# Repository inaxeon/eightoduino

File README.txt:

This is the source code for an Intel 8086 based micro board

Full details are here:
http://tech.mattmillman.com/projects/8od/

Directory contents:

app_*:

Example "boot from flash" applications for 8OD.

bootrom:

The source code for 8OD's standard bootrom which is used
for serial download, to and booting from SPI flash.

eprom_with_app:

Contains an example of how to make an image which runs from
EPROM instead of using the standard bootrom. RAM is still
required to store the stack and data.

Interrupts are not currently supported.

sys:

Sources used by all other subdirectories

*** CAVEAT EMPTOR ***

All code here must be compiled with Open WATCOM version 1.7a

I have tried newer versions - my findings:

Version 1.8
Version 1.9

* Copy attribute (linker script) seems to be broken.
  Linker does not copy data from source segment to destination
  segments, breaking the bootrom builds.

* There seems to be some kind of new enforcement mechanism
  which checks that no code or data lies outside of the active 64KB
  segment. 8OD apps technically do have a little of this to assist
  the bootstrapping process, but it is not an actual problem.
  'wlink' in these versions believes otherwise, and fails to link.

Version 2.0 BETA

* Still has the copy attribute bug

* The segment extent enforcement seems to have disappeared in this
  version, promising...
  
* When I tried to build an app, the .hex were mostly garbage data with
  the majority of the exectuable code missing, suffice to say that this
  version is completely unuseable (at the time I tried it).

Version 1.7a observed problems

* This version isn't perfect either. See in 'app_gravitech_shield' where
  I have had to add dummy code to stop the linker from crashing. I spent
  quite a lot of time investigating this and never got to the bottom
  of it.

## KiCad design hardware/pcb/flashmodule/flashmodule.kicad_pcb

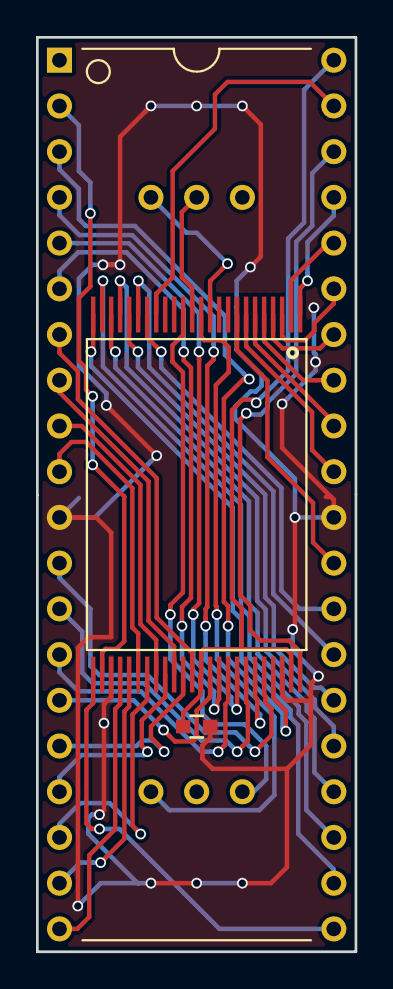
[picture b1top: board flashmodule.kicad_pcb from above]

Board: 2 copper layers, 17.7 x 50.8 mm, 5 parts (0 on the bottom side), 42 nets.

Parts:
C1: 0.1; C_0603
P1, P2: CONN_01X03; Socket_Strip_Straight_1x03
U1: 28F400; TSOP48
U2: M27C4002; DIP-40__600

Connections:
/A0: U1.25, U2.21
/A1: U1.24, U2.22
/A2: U1.23, U2.23
/A3: U1.22, U2.24
/A4: U1.21, U2.25
/A5: U1.20, U2.26
/A6: U1.19, U2.27
/A7: U1.18, U2.28
/A8: U1.8, U2.29
/A9: U1.7, U2.31
/A10: U1.6, U2.32
/A11: U1.5, U2.33
/A12: U1.4, U2.34
/A13: U1.3, U2.35
/A14: U1.2, U2.36
/A15: U1.1, U2.37
/A16: U1.48, U2.38
/A17: U1.17, U2.39
/D0: U1.29, U2.19
/D1: U1.31, U2.18
/D2: U1.33, U2.17
/D3: U1.35, U2.16
/D4: U1.38, U2.15
/D5: U1.40, U2.14
/D6: U1.42, U2.13
/D7: U1.44, U2.12
/D8: U1.30, U2.10
/D9: U1.32, U2.9
/D10: U1.34, U2.8
/D11: U1.36, U2.7
/D12: U1.39, U2.6
/D13: U1.41, U2.5
/D14: U1.43, U2.4
/D15: U1.45, U2.3
/VPP: P1.2, U1.13
/~CS: U1.26, U2.2
/~RD: U1.28, U2.20
/~RESET: P2.1, U1.12
/~WP: P2.3, U1.14
/~WR: P1.1, U1.11
GND: C1.2, U1.27, U1.46, U2.11, U2.30
VCC: C1.1, U1.37, U1.47, U2.40

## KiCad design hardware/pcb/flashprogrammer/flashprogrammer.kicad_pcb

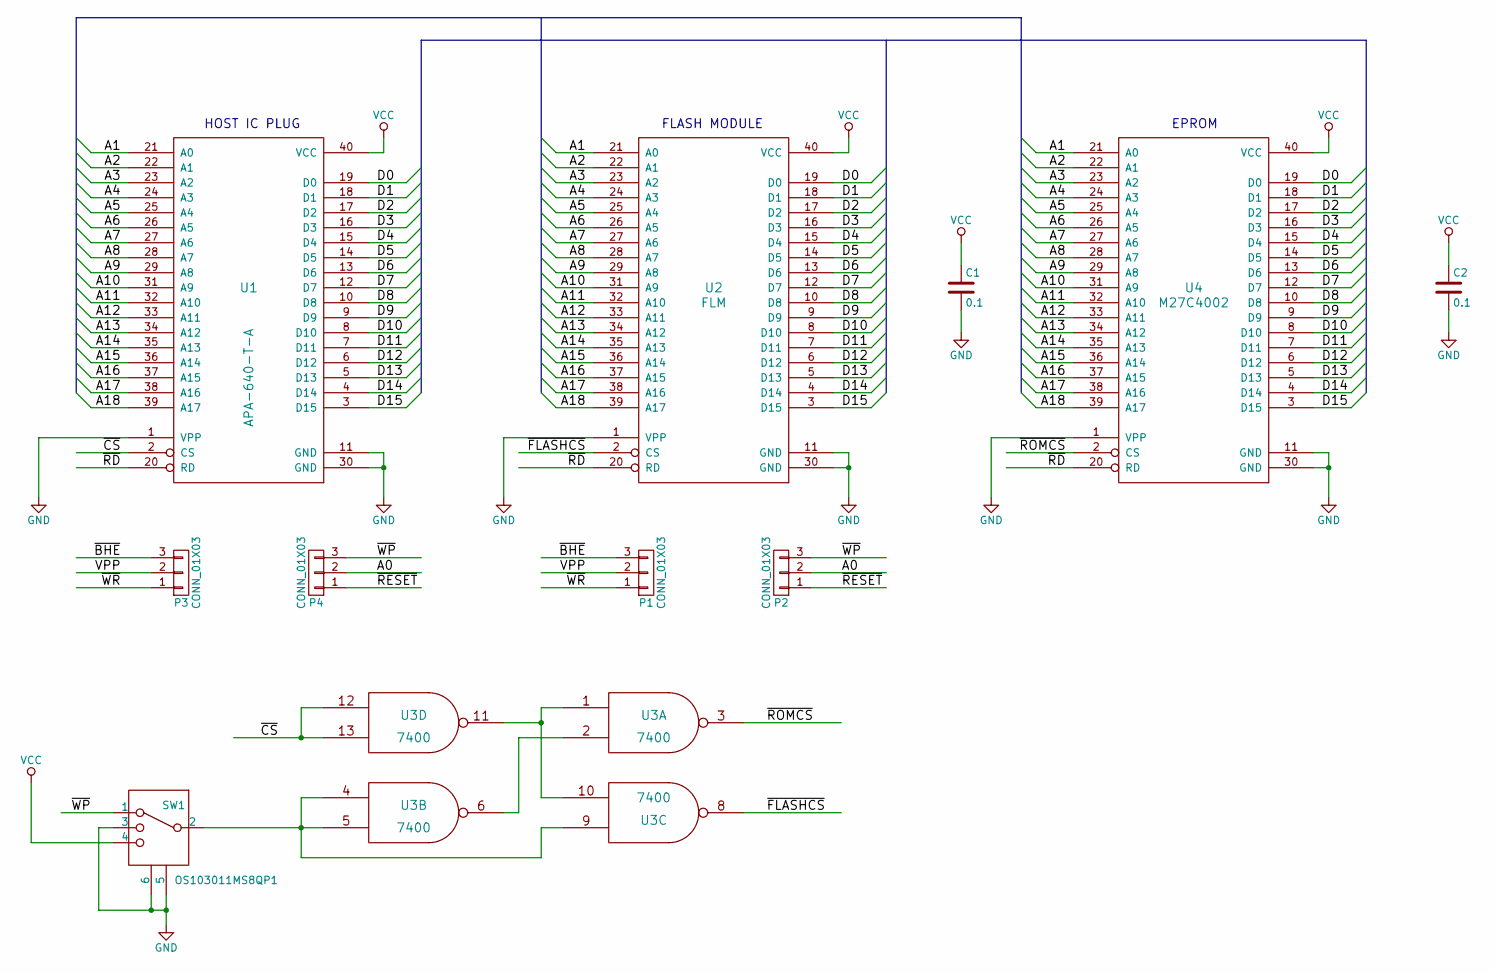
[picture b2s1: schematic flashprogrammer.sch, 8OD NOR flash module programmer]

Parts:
C1, C2: 0.1; C_0603
P1, P2, P3, P4: CONN_01X03; Socket_Strip_Straight_1x03
SW1: OS103011MS8QP1; SW_SP3T
U1: APA-640-T-A; DIP-40__600
U2: FLM; DIP-40__600
U3: 7400; SOIC-14_3.9x8.7mm_Pitch1.27mm
U4: M27C4002; DIP-40__600

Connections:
/A0: P2.2, P4.2
/A1: U1.21 (A0), U2.21 (A0), U4.21 (A0)
/A2: U1.22 (A1), U2.22 (A1), U4.22 (A1)
/A3: U1.23 (A2), U2.23 (A2), U4.23 (A2)
/A4: U1.24 (A3), U2.24 (A3), U4.24 (A3)
/A5: U1.25 (A4), U2.25 (A4), U4.25 (A4)
/A6: U1.26 (A5), U2.26 (A5), U4.26 (A5)
/A7: U1.27 (A6), U2.27 (A6), U4.27 (A6)
/A8: U1.28 (A7), U2.28 (A7), U4.28 (A7)
/A9: U1.29 (A8), U2.29 (A8), U4.29 (A8)
/A10: U1.31 (A9), U2.31 (A9), U4.31 (A9)
/A11: U1.32 (A10), U2.32 (A10), U4.32 (A10)
/A12: U1.33 (A11), U2.33 (A11), U4.33 (A11)
/A13: U1.34 (A12), U2.34 (A12), U4.34 (A12)
/A14: U1.35 (A13), U2.35 (A13), U4.35 (A13)
/A15: U1.36 (A14), U2.36 (A14), U4.36 (A14)
/A16: U1.37 (A15), U2.37 (A15), U4.37 (A15)
/A17: U1.38 (A16), U2.38 (A16), U4.38 (A16)
/A18: U1.39 (A17), U2.39 (A17), U4.39 (A17)
/D0: U1.19 (D0), U2.19 (D0), U4.19 (D0)
/D1: U1.18 (D1), U2.18 (D1), U4.18 (D1)
/D2: U1.17 (D2), U2.17 (D2), U4.17 (D2)
/D3: U1.16 (D3), U2.16 (D3), U4.16 (D3)
/D4: U1.15 (D4), U2.15 (D4), U4.15 (D4)
/D5: U1.14 (D5), U2.14 (D5), U4.14 (D5)
/D6: U1.13 (D6), U2.13 (D6), U4.13 (D6)
/D7: U1.12 (D7), U2.12 (D7), U4.12 (D7)
/D8: U1.10 (D8), U2.10 (D8), U4.10 (D8)
/D9: U1.9 (D9), U2.9 (D9), U4.9 (D9)
/D10: U1.8 (D10), U2.8 (D10), U4.8 (D10)
/D11: U1.7 (D11), U2.7 (D11), U4.7 (D11)
/D12: U1.6 (D12), U2.6 (D12), U4.6 (D12)
/D13: U1.5 (D13), U2.5 (D13), U4.5 (D13)
/D14: U1.4 (D14), U2.4 (D14), U4.4 (D14)
/D15: U1.3 (D15), U2.3 (D15), U4.3 (D15)
/VPP: P1.2, P3.2
/~BHE: P1.3, P3.3
/~CS: U1.2 (CS), U3.12, U3.13
/~FLASHCS: U2.2 (CS), U3.8
/~RD: U1.20 (RD), U2.20 (RD), U4.20 (RD)
/~RESET: P2.1, P4.1
/~ROMCS: U3.3, U4.2 (CS)
/~WP: P2.3, P4.3, SW1.1
/~WR: P1.1, P3.1
GND: C1.2, C2.2, SW1.3, SW1.5, SW1.6, U1.1 (VPP), U1.11 (GND), U1.30 (GND), U2.1 (VPP), U2.11 (GND), U2.30 (GND), U3.7 (GND), U4.1 (VPP), U4.11 (GND), U4.30 (GND)
unnamed: SW1.2, U3.4, U3.5, U3.9
unnamed: U3.1, U3.10, U3.11
unnamed: U3.2, U3.6
VCC: C1.1, C2.1, SW1.4, U1.40 (VCC), U2.40 (VCC), U3.14 (VCC), U4.40 (VCC)

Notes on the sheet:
HOST IC PLUG
FLASH MODULE
EPROM

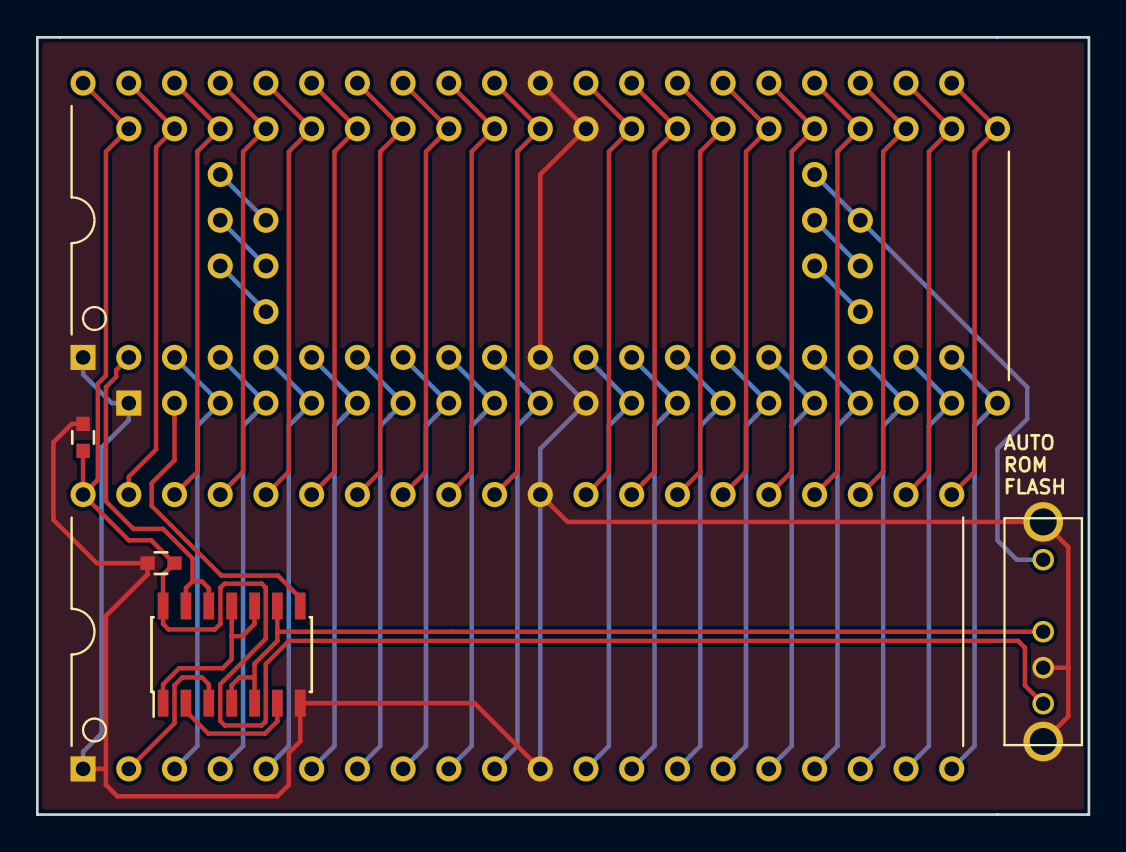
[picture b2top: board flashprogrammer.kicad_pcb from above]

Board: 2 copper layers, 58.4 x 43.2 mm, 11 parts (0 on the bottom side), 49 nets.

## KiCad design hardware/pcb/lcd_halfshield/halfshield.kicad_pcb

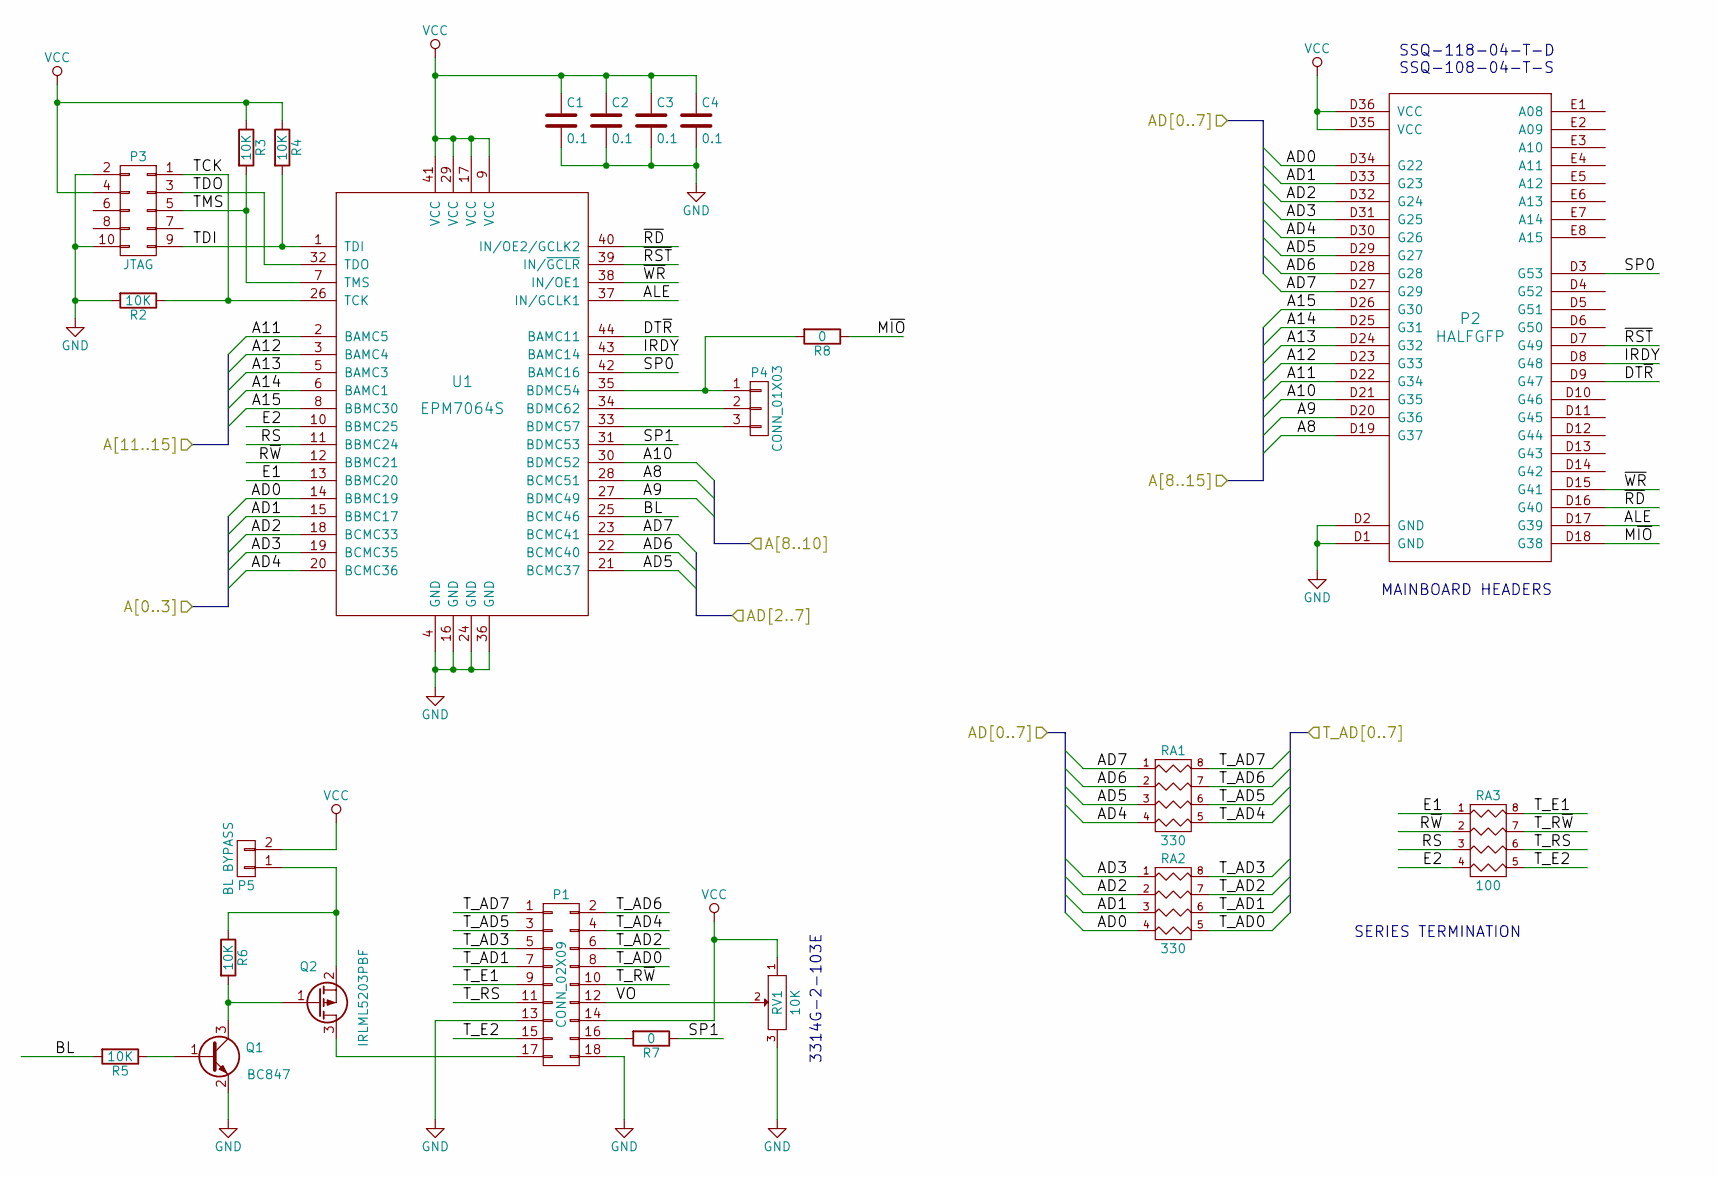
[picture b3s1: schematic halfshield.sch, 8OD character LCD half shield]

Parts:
C1, C2, C3, C4: 0.1; C_0603
P1: CONN_02X09; PIN_ARRAY_9x2
P2: HALFGFP; DUINO
P3: JTAG; PIN_ARRAY_5x2
P4: CONN_01X03; Pin_Header_Straight_1x03
P5: BL BYPASS; Pin_Header_Straight_1x02
Q1: BC847; SOT-23
Q2: IRLML5203PBF
R2, R3, R4, R5, R6: 10K; R_0603
R7, R8: 0; R_0603
RA1, RA2: 330; R_Array_Convex_4x0603
RA3: 100; R_Array_Convex_4x0603
RV1: 10K; POT_SMD
U1: EPM7064S; TQFP-44_10x10mm_Pitch0.8mm

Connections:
/A8: P2.D19 (G37), U1.28 (BCMC51)
/A9: P2.D20 (G36), U1.27 (BDMC49)
/A10: P2.D21 (G35), U1.30 (BDMC52)
/A11: P2.D22 (G34), U1.2 (BAMC5)
/A12: P2.D23 (G33), U1.3 (BAMC4)
/A13: P2.D24 (G32), U1.5 (BAMC3)
/A14: P2.D25 (G31), U1.6 (BAMC1)
/A15: P2.D26 (G30), U1.8 (BBMC30)
/AD0: P2.D34 (G22), RA2.4, U1.14 (BBMC19)
/AD1: P2.D33 (G23), RA2.3, U1.15 (BBMC17)
/AD2: P2.D32 (G24), RA2.2, U1.18 (BCMC33)
/AD3: P2.D31 (G25), RA2.1, U1.19 (BCMC35)
/AD4: P2.D30 (G26), RA1.4, U1.20 (BCMC36)
/AD5: P2.D29 (G27), RA1.3, U1.21 (BCMC37)
/AD6: P2.D28 (G28), RA1.2, U1.22 (BCMC40)
/AD7: P2.D27 (G29), RA1.1, U1.23 (BCMC41)
/ALE: P2.D17 (G39), U1.37 (IN/GCLK1)
/BL: R5.2, U1.25 (BCMC46)
/DT~R: P2.D9 (G47), U1.44 (BAMC11)
/E1: RA3.1, U1.13 (BBMC20)
/E2: RA3.4, U1.10 (BBMC25)
/IRDY: P2.D8 (G48), U1.43 (BAMC14)
/M~IO: P2.D18 (G38), R8.1
/RS: RA3.3, U1.11 (BBMC24)
/R_AD0: P1.8, RA2.5 (R4)
/R_AD1: P1.7, RA2.6 (R3)
/R_AD2: P1.6, RA2.7 (R2)
/R_AD3: P1.5, RA2.8 (R1)
/R_AD4: P1.4, RA1.5 (R4)
/R_AD5: P1.3, RA1.6 (R3)
/R_AD6: P1.2, RA1.7 (R2)
/R_AD7: P1.1, RA1.8 (R1)
/R_E1: P1.9, RA3.8 (R1)
/R_E2: P1.15, RA3.5 (R4)
/R_RS: P1.11, RA3.6 (R3)
/R_R~W: P1.10, RA3.7 (R2)
/R~W: RA3.2, U1.12 (BBMC21)
/SP0: P2.D3 (G53), U1.42 (BAMC16)
/SP1: R7.1, U1.31 (BDMC53)
/TCK: P3.1, R2.1, U1.26 (TCK)
/TDI: P3.9, R4.2, U1.1 (TDI)
/TDO: P3.3, U1.32 (TDO)
/TMS: P3.5, R3.2, U1.7 (TMS)
/VO: P1.12, RV1.2
/~RD: P2.D16 (G40), U1.40 (IN/OE2/GCLK2)
/~RST: P2.D7 (G49), U1.39 (IN/~GCLR)
/~WR: P2.D15 (G41), U1.38 (IN/OE1)
GND: C1.2, C2.2, C3.2, C4.2, P1.13, P1.18, P2.D1 (GND), P2.D2 (GND), P3.2, P3.10, Q1.2 (E), R2.2, RV1.3, U1.4 (GND), U1.16 (GND), U1.24 (GND), U1.36 (GND)
unnamed: P1.16, R7.2
unnamed: P1.17, Q2.3 (D)
unnamed: P4.1, R8.2, U1.35 (BDMC54)
unnamed: P4.2, U1.34 (BDMC62)
unnamed: P4.3, U1.33 (BDMC57)
unnamed: P5.1, Q2.2 (S), R6.1
unnamed: Q1.1 (B), R5.1
unnamed: Q1.3 (C), Q2.1 (G), R6.2
VCC: C1.1, C2.1, C3.1, C4.1, P1.14, P2.D35 (VCC), P2.D36 (VCC), P3.4, P5.2, R3.1, R4.1, RV1.1, U1.9 (VCC), U1.17 (VCC), U1.29 (VCC), U1.41 (VCC)

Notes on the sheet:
SSQ-118-04-T-D SSQ-108-04-T-S
3314G-2-103E
SERIES TERMINATION
MAINBOARD HEADERS

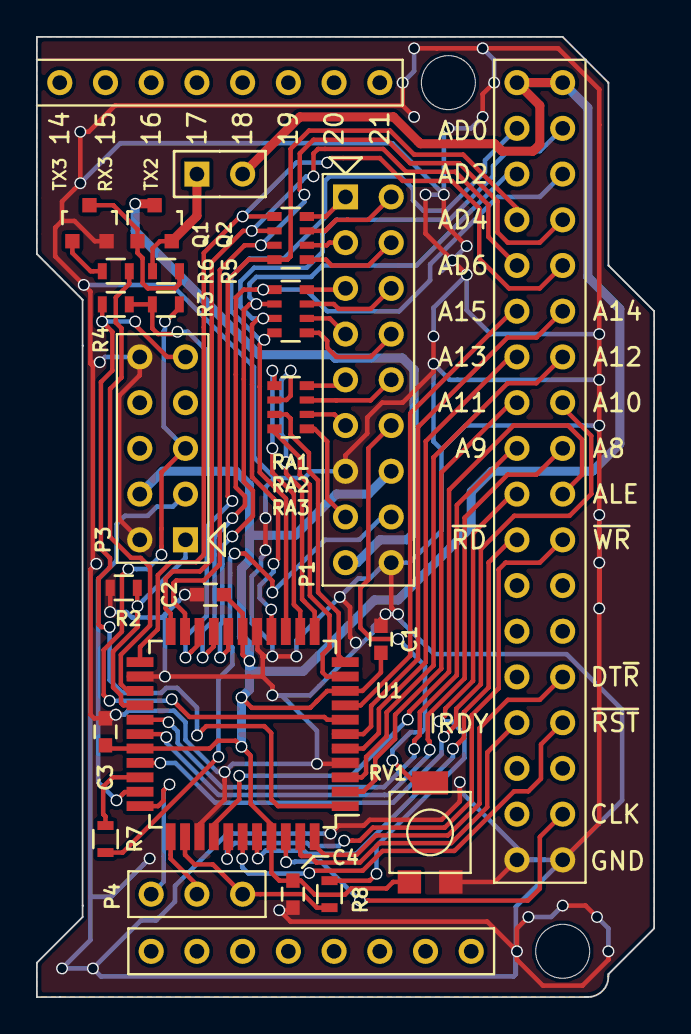
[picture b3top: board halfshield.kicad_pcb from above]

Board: 2 copper layers, 34.3 x 53.3 mm, 23 parts (0 on the bottom side), 57 nets.

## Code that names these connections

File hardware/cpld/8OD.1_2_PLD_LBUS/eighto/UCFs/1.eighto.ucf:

// UCF file for 8OD revision 1 (Blue)


NET EXTWR LOC=P153;
NET EXTRD LOC=P154;

NET ALE LOC=P151;
NET MIO LOC=P152;
NET RESET LOC=P159;
NET SYSCLK LOC=P150;
NET CPUCLK LOC=P22;
NET BHE LOC=P155;
NET ULE LOC=P52;
NET UHE LOC=P49;
NET DEN LOC=P102;
NET MRST LOC=P98;
NET NMI LOC=P64;
NET CPU10 LOC=P149;
NET BHEQ LOC=P23;
NET MIDCLK LOC=P53;
NET MIDCS LOC=P54;
NET DTR LOC=P50;
NET I2CCS LOC=P83;
NET RDY LOC=P24;
NET PGMRXD LOC=P101;
NET EEWP LOC=P97;
NET WDI LOC=P96;

NET ROMCS LOC=P48;
NET RAMCS LOC=P77;

NET UCSA LOC=P68;
NET UCSB LOC=P72;
NET UCSC LOC=P60;
NET UCSD LOC=P57;

NET TXA LOC=P76;
NET TXB LOC=P74;
NET TXC LOC=P59;
NET TXD LOC=P58;

NET RXA LOC=P66;
NET RXB LOC=P65;
NET RXC LOC=P63;
NET RXD LOC=P55;

NET IRQ1 LOC=P67;
NET IRQ2 LOC=P69;
NET IRQ3 LOC=P62;
NET IRQ4 LOC=P56;

NET AD_E<0> LOC=P21;
NET AD_E<1> LOC=P19;
NET AD_E<2> LOC=P18;
NET AD_E<3> LOC=P17;
NET AD_E<4> LOC=P16;
NET AD_E<5> LOC=P15;
NET AD_E<6> LOC=P14;
NET AD_E<7> LOC=P13;
NET AD_E<8> LOC=P12;
NET AD_E<9> LOC=P11;
NET AD_E<10> LOC=P9;
NET AD_E<11> LOC=P8;
NET AD_E<12> LOC=P7;
NET AD_E<13> LOC=P6;
NET AD_E<14> LOC=P5;
NET AD_E<15> LOC=P4;

NET AQ<0> LOC=P47;
NET AQ<1> LOC=P36;
NET AQ<2> LOC=P37;
NET AQ<3> LOC=P38;
NET AQ<4> LOC=P39;
NET AQ<5> LOC=P45;
NET AQ<6> LOC=P44;
NET AQ<7> LOC=P43;
NET AQ<8> LOC=P42;
NET AQ<9> LOC=P35;
NET AQ<10> LOC=P34;
NET AQ<11> LOC=P33;
NET AQ<12> LOC=P32;
NET AQ<13> LOC=P30;
NET AQ<14> LOC=P29;
NET AQ<15> LOC=P28;
NET AQ<16> LOC=P27;
NET AQ<17> LOC=P26;
NET AQ<18> LOC=P25;

NET A<19> LOC=P156;
NET A<18> LOC=P158;
NET A<17> LOC=P2;
NET A<16> LOC=P3;

NET PORTA<0> LOC=P132;
NET PORTA<1> LOC=P133;
NET PORTA<2> LOC=P134;
NET PORTA<3> LOC=P135;
NET PORTA<4> LOC=P138;
NET PORTA<5> LOC=P139;
NET PORTA<6> LOC=P140;
NET PORTA<7> LOC=P142;
NET PORTA<8> LOC=P143;
NET PORTA<9> LOC=P144;
NET PORTA<10> LOC=P145;
NET PORTA<11> LOC=P146;
NET PORTA<12> LOC=P147;
NET PORTA<13> LOC=P148;
NET PORTA<14> LOC=P131;
NET PORTA<15> LOC=P130;

NET PORTB<0> LOC=P129;
NET PORTB<1> LOC=P128;
NET PORTB<2> LOC=P126;
NET PORTB<3> LOC=P125;
NET PORTB<4> LOC=P124;
NET PORTB<5> LOC=P123;

NET LBUS_AD<0> LOC=P119;
NET LBUS_AD<1> LOC=P122;
NET LBUS_AD<2> LOC=P117;
NET LBUS_AD<3> LOC=P118;
NET LBUS_AD<4> LOC=P115;
NET LBUS_AD<5> LOC=P116;
NET LBUS_AD<6> LOC=P113;
NET LBUS_AD<7> LOC=P114;

NET LBUS_A<8> LOC=P105;
NET LBUS_A<9> LOC=P104;
NET LBUS_A<10> LOC=P107;
NET LBUS_A<11> LOC=P106;
NET LBUS_A<12> LOC=P109;
NET LBUS_A<13> LOC=P108;
NET LBUS_A<14> LOC=P112;
NET LBUS_A<15> LOC=P111;
NET LBUS_A<16> LOC=P89;
NET LBUS_A<17> LOC=P88;
NET LBUS_A<18> LOC=P91;
NET LBUS_A<19> LOC=P90;

NET LBUS_RD LOC=P92;
NET LBUS_WR LOC=P93;
NET LBUS_DTR LOC=P87;
NET LBUS_DEN LOC=P86;
NET LBUS_ALE LOC=P103;
NET LBUS_RST LOC=P85;
NET LBUS_MIO LOC=P95;
NET LBUS_IRDY LOC=P84;
NET LBUS_CLK LOC=P79;

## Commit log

2019-02-18 Updated hveprom app for new hardware, also added AVR port
2019-04-08 Changes for second board red
2019-04-12 Removed object file
2019-04-12 New pinout of second rev of 2708 board
2019-04-12 Updated gitignore
2019-04-12 Fixed build error
2019-08-23 Added HEX file
2019-08-28 Re-added hex
2019-08-28 Revert
2019-08-28 Added RS-232 build
2019-08-28 Removed unneeded fuse settings
2019-09-07 Added hardware test
2019-09-07 Updated RS232 version
2019-12-23 Fixed issue with 115200 baud
2020-05-19 Added 5MHz x86 option
2020-07-22 MCS48 WIP
2020-07-25 8748/8749H working
2020-07-25 MCS48 working better
2020-07-25 MCS48 Bump post write delay, fixed zero write count bug
2020-08-15 804x added
2020-08-15 804x error check
2020-08-16 MCS48 timings
2020-08-16 Slow mode byte
2020-08-17 Got 8741 working
2020-08-18 Removed slow mode
2020-08-18 Moved 8741 logic to correct place
2020-09-20 Fixed bug in write counter
2020-10-04 Fixed bug in MCS-48 hardware test
2020-10-04 RS-232 version updated
2020-10-04 Switch for RS232 build
2020-10-04 Fixed bug where 8048/49 was rejected
2020-10-24 8OD timings, removed delay after latch of read address causing clash
2020-12-27 Added 8050
2020-12-27 Updated HW test
2020-12-27 Revert to USB interface
2021-04-01 Set shield to invalid when straps aren't fitted
2021-04-09 Actually return ERR_NO_DEV when there's no shield attached stupid
2021-04-13 Added 8755
2021-11-29 Added compile howto
2022-11-04 TMS2716 WIP
2022-11-04 TMS2716 initial implementation complete
2022-11-16 Rename signals to emphasize new push/pull mode
2022-11-26 Hardware test passing
2022-11-28 Fixed various problems found while testing
2022-11-28 Simplify
2022-11-28 Removed unneeded code
2022-11-28 Restore original scheme for MCM6876x
2022-11-29 Updated comments
2022-12-03 Fixed 270x RD pin startup state. Update MCS48 for new 8755 adapter
2022-12-09 Updated HEX files
2025-10-26 Added HW stuff
